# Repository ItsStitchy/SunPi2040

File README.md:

# SunPi2040 ☀️

This is my custom development board powered by the **RP2040** chip. 

Instead of just cheating and throwing a pre-made Raspberry Pi Pico or a Seeed XIAO onto a blank board, I wanted to learn how to route the actual raw microcontroller silicon entirely from scratch. 

It's built for my **Hack Club Macondo** hardware project!

## 🚀 What's on it?
* **RP2040 Microcontroller:**
* **LED** There's one LED that works as a status light
* **16MB Flash Memory:** (Winbond W25Q128) so I have plenty of space to flash scripts.
* **USB-C Port:** For power and data, because Micro-USB belongs in the trash.
* **AMS1117-3.3V:** To drop the USB power down safely so the chip doesn't explode.
* **Pin Headers:** Two rows of 20-pin headers so I can actually plug this into a breadboard.

The PCB was designed using KiCAD, and I went from never even touching hardware design to creating this devboard. Along the way, I struggled with lots of issues like DRC errors and terrible routing where I met a lot of dead ends.
I created this project in order to learn how to work with KiCAD and hardware design, so that I can work on another project which is a game console-style project.
I found PCB easter eggs quite amusing, and so I decided to include a bunch of PCB easter eggs at the back.

Pictures of the Devboard:

Open source, feel free to check out my schematics or tell me where my routing looks messy.

Attached are the images of the schematic and the PCB

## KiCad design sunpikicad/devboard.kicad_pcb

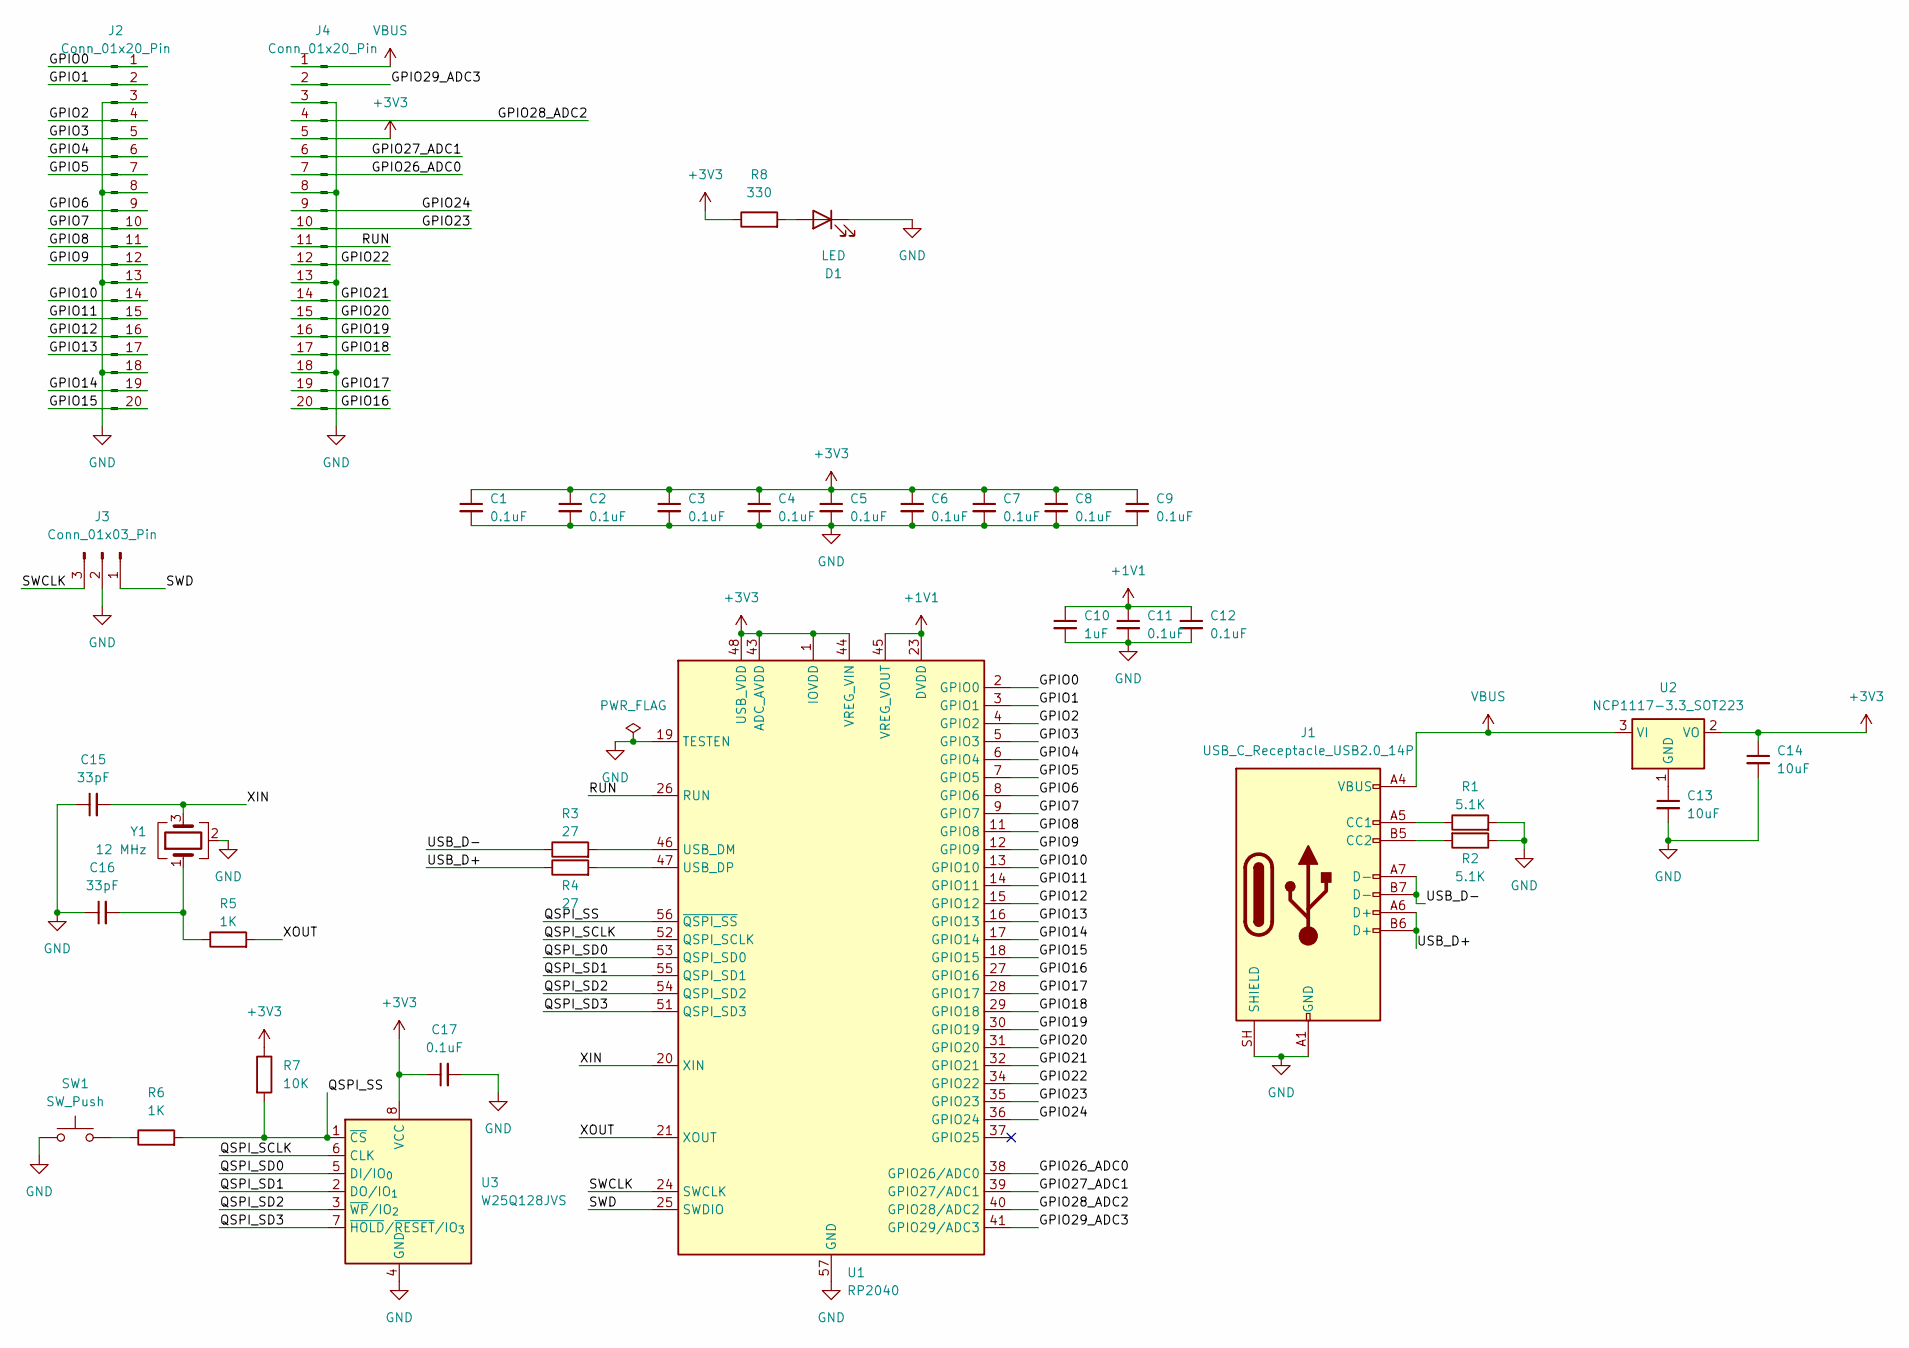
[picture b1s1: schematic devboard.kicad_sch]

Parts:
C1, C2, C3, C4, C5, C6, C7, C8, C9, C11, C12, C17: 0.1uF; C_0603_1608Metric
C10: 1uF; C_0603_1608Metric
C13, C14: 10uF; C_0603_1608Metric
C15, C16: 33pF; C_0603_1608Metric
D1: LED; LED_1206_3216Metric_ReverseMount_Hole1.8x2.4mm
J1: USB_C_Receptacle_USB2.0_14P; USB_C_Receptacle_GCT_USB4105-xx-A_16P_TopMnt_Horizontal
J2, J4: Conn_01x20_Pin; PinHeader_1x20_P2.54mm_Vertical
J3: Conn_01x03_Pin; PinHeader_1x03_P2.54mm_Vertical
R1, R2: 5.1K; R_0603_1608Metric
R3, R4: 27; R_0603_1608Metric
R5, R6: 1K; R_0603_1608Metric
R7: 10K; R_0603_1608Metric
R8: 330; R_0603_1608Metric
SW1: SW_Push; SW_Push_SPST_NO_Alps_SKRK
U1: RP2040; QFN-56-1EP_7x7mm_P0.4mm_EP3.2x3.2mm
U2: NCP1117-3.3_SOT223; SOT-223-3_TabPin2
U3: W25Q128JVS; SOIC-8_5.3x5.3mm_P1.27mm
Y1: 12 MHz; Crystal_SMD_3225-4Pin_3.2x2.5mm

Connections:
+1V1: C10.1, C11.1, C12.1, U1.23 (DVDD), U1.45 (VREG_VOUT), U1.50 (DVDD)
+3V3: C1.1, C2.1, C3.1, C4.1, C5.1, C6.1, C7.1, C8.1, C9.1, C14.1, C17.1, J4.5, R7.1, R8.1, U1.1 (IOVDD), U1.10 (IOVDD), U1.22 (IOVDD), U1.33 (IOVDD), U1.42 (IOVDD), U1.43 (ADC_AVDD), U1.44 (VREG_VIN), U1.48 (USB_VDD), U1.49 (IOVDD), U2.2 (VO), U3.8 (VCC)
/GPIO0: J2.1, U1.2 (GPIO0)
/GPIO1: J2.2, U1.3 (GPIO1)
/GPIO2: J2.4, U1.4 (GPIO2)
/GPIO3: J2.5, U1.5 (GPIO3)
/GPIO4: J2.6, U1.6 (GPIO4)
/GPIO5: J2.7, U1.7 (GPIO5)
/GPIO6: J2.9, U1.8 (GPIO6)
/GPIO7: J2.10, U1.9 (GPIO7)
/GPIO8: J2.11, U1.11 (GPIO8)
/GPIO9: J2.12, U1.12 (GPIO9)
/GPIO10: J2.14, U1.13 (GPIO10)
/GPIO11: J2.15, U1.14 (GPIO11)
/GPIO12: J2.16, U1.15 (GPIO12)
/GPIO13: J2.17, U1.16 (GPIO13)
/GPIO14: J2.19, U1.17 (GPIO14)
/GPIO15: J2.20, U1.18 (GPIO15)
/GPIO16: J4.20, U1.27 (GPIO16)
/GPIO17: J4.19, U1.28 (GPIO17)
/GPIO18: J4.17, U1.29 (GPIO18)
/GPIO19: J4.16, U1.30 (GPIO19)
/GPIO20: J4.15, U1.31 (GPIO20)
/GPIO21: J4.14, U1.32 (GPIO21)
/GPIO22: J4.12, U1.34 (GPIO22)
/GPIO23: J4.10, U1.35 (GPIO23)
/GPIO24: J4.9, U1.36 (GPIO24)
/GPIO26_ADC0: J4.7, U1.38 (GPIO26/ADC0)
/GPIO27_ADC1: J4.6, U1.39 (GPIO27/ADC1)
/GPIO28_ADC2: J4.4, U1.40 (GPIO28/ADC2)
/GPIO29_ADC3: J4.2, U1.41 (GPIO29/ADC3)
/QSPI_SCLK: U1.52 (QSPI_SCLK), U3.6 (CLK)
/QSPI_SD0: U1.53 (QSPI_SD0), U3.5 (DI/IO_{0})
/QSPI_SD1: U1.55 (QSPI_SD1), U3.2 (DO/IO_{1})
/QSPI_SD2: U1.54 (QSPI_SD2), U3.3 (~WP/IO_{2})
/QSPI_SD3: U1.51 (QSPI_SD3), U3.7 (~HOLD/~RESET/IO_{3})
/QSPI_SS: R6.2, R7.2, U1.56 (~QSPI_SS), U3.1 (~CS)
/RUN: J4.11, U1.26 (RUN)
/SWCLK: J3.3, U1.24 (SWCLK)
/SWD: J3.1, U1.25 (SWDIO)
/USB_D+: J1.A6 (D+), J1.B6 (D+), R4.1
/USB_D-: J1.A7 (D-), J1.B7 (D-), R3.1
/XIN: C15.2, U1.20 (XIN), Y1.3
/XOUT: R5.2, U1.21 (XOUT)
GND: C1.2, C2.2, C3.2, C4.2, C5.2, C6.2, C7.2, C8.2, C9.2, C10.2, C11.2, C12.2, C13.2, C14.2, C15.1, C16.1, C17.2, D1.1 (K), J1.A1 (GND), J1.A12 (GND), J1.B1 (GND), J1.B12 (GND), J1.SH (SHIELD), J2.3, J2.8, J2.13, J2.18, J3.2, J4.3, J4.8, J4.13, J4.18, R1.2, R2.1, SW1.1, U1.19 (TESTEN), U1.57 (GND), U3.4 (GND), Y1.2 (G), Y1.4 (G)
unnamed: C16.2, R5.1, Y1.1
unnamed: D1.2 (A), R8.2
unnamed: J1.A5 (CC1), R1.1
unnamed: J1.B5 (CC2), R2.2
unnamed: R6.1, SW1.2
unnamed: R3.2, U1.46 (USB_DM)
unnamed: R4.2, U1.47 (USB_DP)
unnamed: C13.1, U2.1 (GND)
VBUS: J1.A4 (VBUS), J1.A9 (VBUS), J1.B4 (VBUS), J1.B9 (VBUS), J4.1, U2.3 (VI)

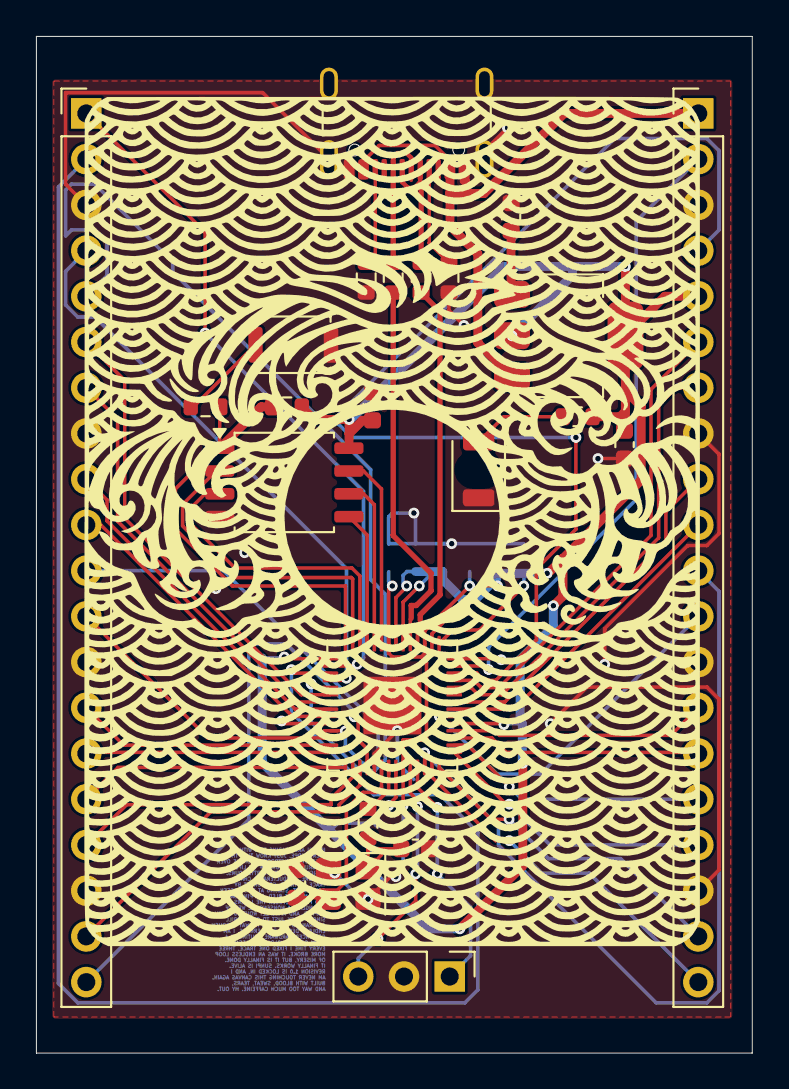
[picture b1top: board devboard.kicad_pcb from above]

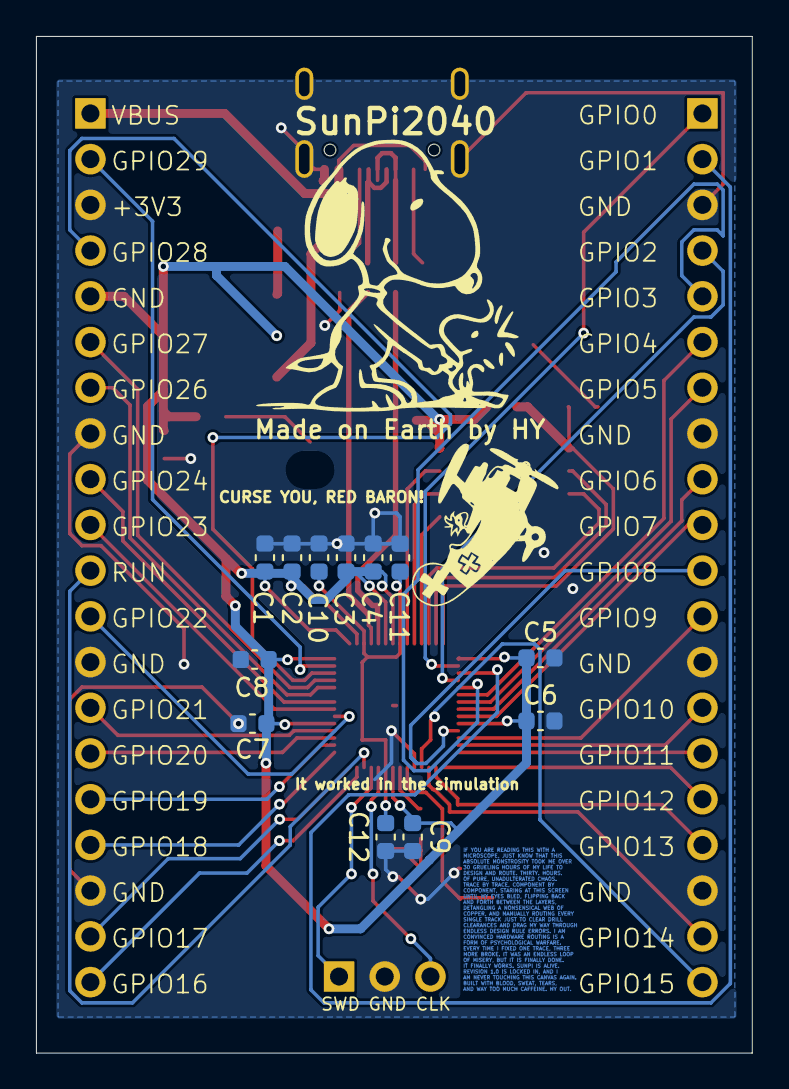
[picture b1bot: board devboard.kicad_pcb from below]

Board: 2 copper layers, 39.8 x 56.5 mm, 35 parts (12 on the bottom side), 54 nets.

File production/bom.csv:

Designator,Footprint,Quantity,Value,LCSC Part #
"C1, C11, C12, C17, C2, C3, C4, C5, C6, C7, C8, C9",0603,12,0.1uF,
C10,0603,1,1uF,
"C13, C14",0603,2,10uF,
"C15, C16",0603,2,33pF,
D1,1206,1,LED,
J1,USB_C_Receptacle_GCT_USB4105-xx-A_16P_TopMnt_Horizontal,1,USB_C_Receptacle_USB2.0_14P,
"J2, J4",PinHeader_1x20_P2.54mm_Vertical,2,Conn_01x20_Pin,
J3,PinHeader_1x03_P2.54mm_Vertical,1,Conn_01x03_Pin,
"R1, R2",0603,2,5.1K,
"R3, R4",0603,2,27,
"R5, R6",0603,2,1K,
R7,0603,1,10K,
R8,0603,1,330,
SW1,SW_Push_SPST_NO_Alps_SKRK,1,SW_Push,
U1,QFN-56-1EP_7x7mm_P0.4mm_EP3.2x3.2mm,1,RP2040,
U2,SOT-223-3_TabPin2,1,NCP1117-3.3_SOT223,
U3,SOIC-8_5.3x5.3mm_P1.27mm,1,W25Q128JVS,
Y1,Crystal_SMD_3225-4Pin_3.2x2.5mm,1,12 MHz,

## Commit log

2026-06-01 Production Files uploaded
    these are the production files I used to upload on JLCPCB
2026-06-01 KiCAD files
2026-06-01 Uploaded schematic and pcb diagrams, footprints
2026-06-01 Create LICENSE
2026-06-26 Modify BOM with new product entries
    Updated product details and added LCSC components.
2026-06-26 Update LCSC Components entry in bom.csv
    Removed the amount for LCSC Components in bom.csv.
2026-06-26 Modify BOM with new product entries and costs
    Updated product details and costs in the BOM.
